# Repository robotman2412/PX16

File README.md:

# Pixie 16
A 16-bit simple-as-possible\* RISC CPU.
Has conditional `MOV` instructions (which is also how branching happens),
And a few math instructions.

Has 4 general registers: `R0`, `R1`, `R2`, `R3`
And 3 special registers: `ST` (stack register), `PF` (flags register), `PC` (program counter)

64K x 16bit memory.

### Note:
RISC is not equal to RISC-V.

PX16 cannot address bytes.

# TODO
Stuf i do be workin on:
- PCB edition
- Emulator
- Finalise MMIO Hardware
- C Compiler

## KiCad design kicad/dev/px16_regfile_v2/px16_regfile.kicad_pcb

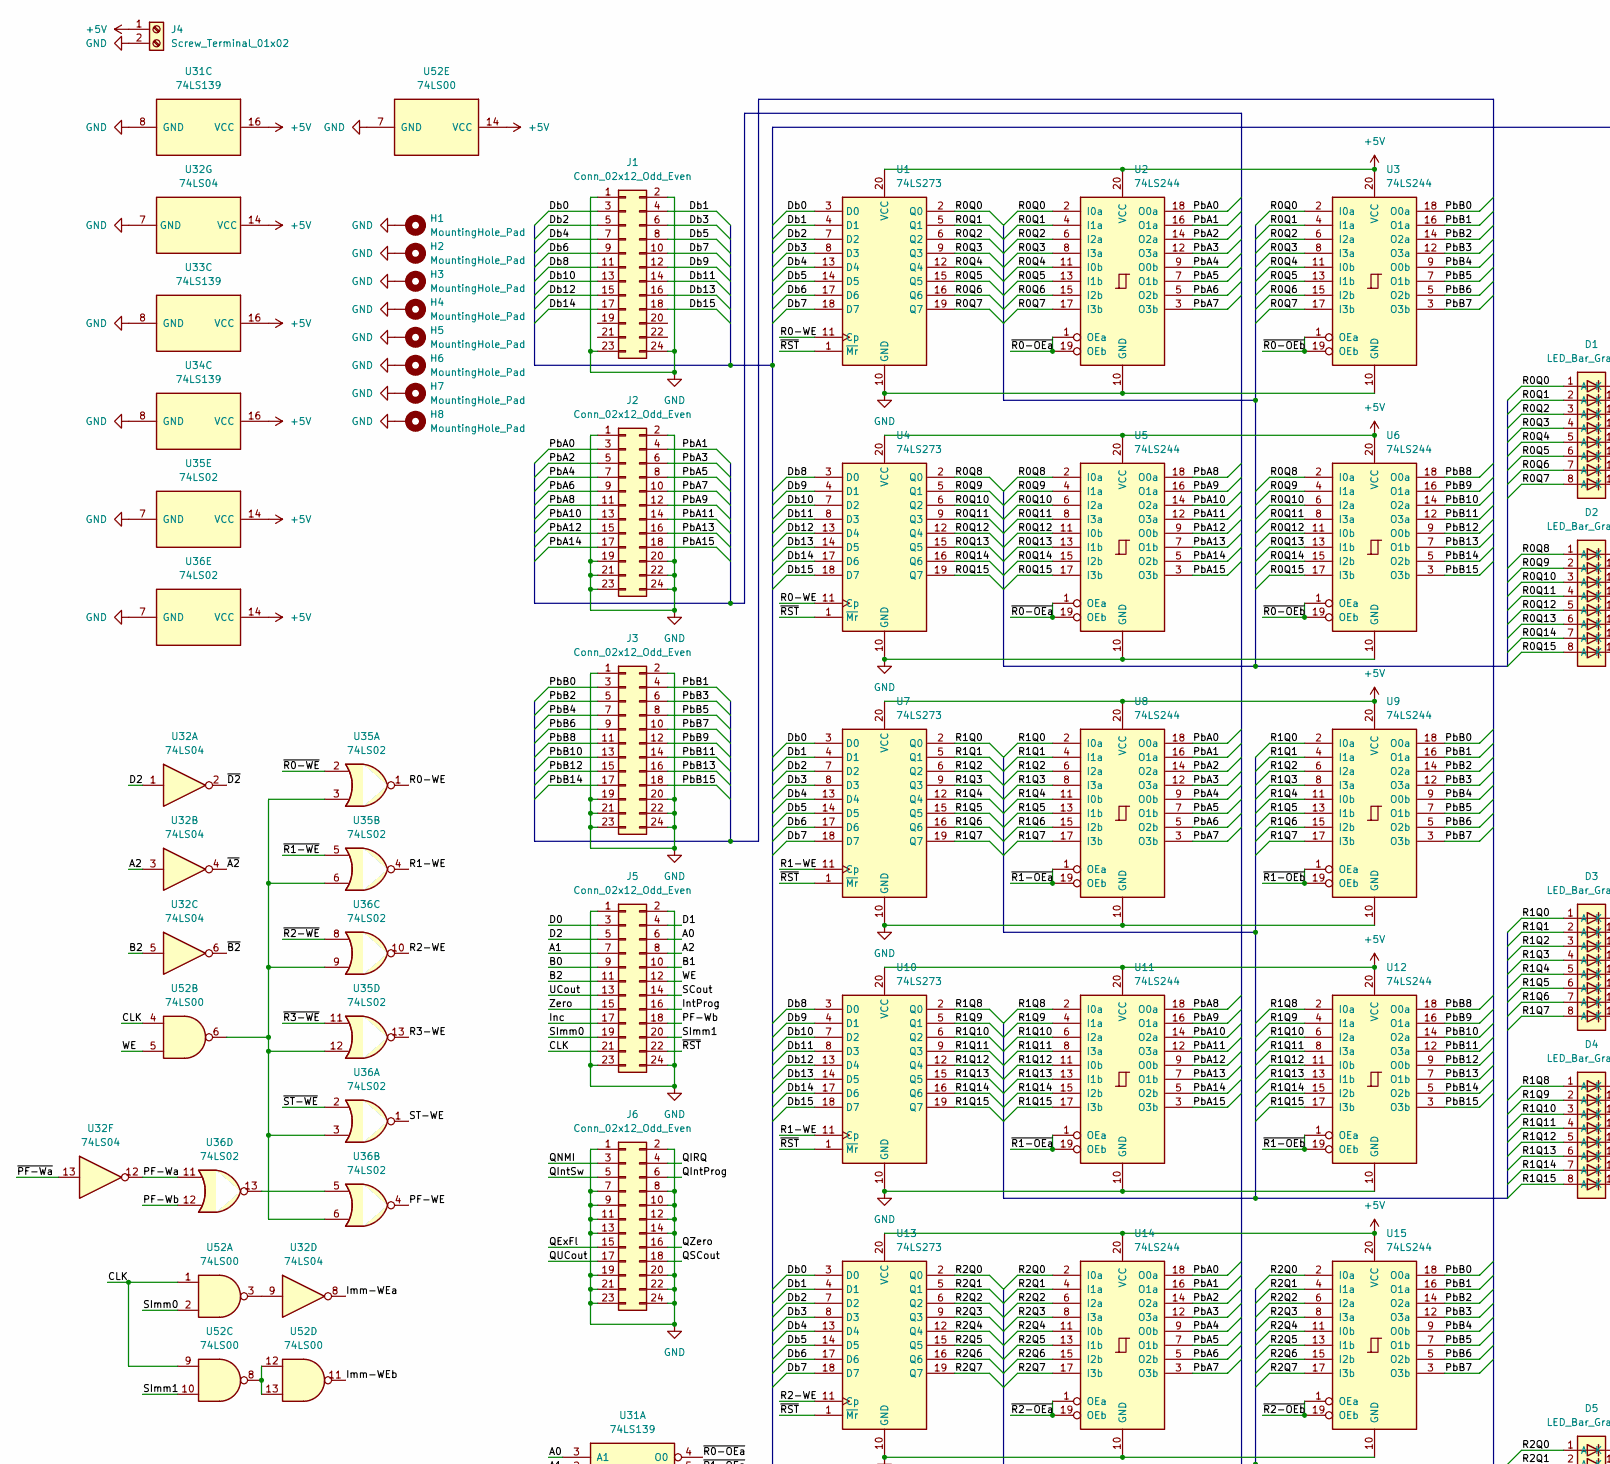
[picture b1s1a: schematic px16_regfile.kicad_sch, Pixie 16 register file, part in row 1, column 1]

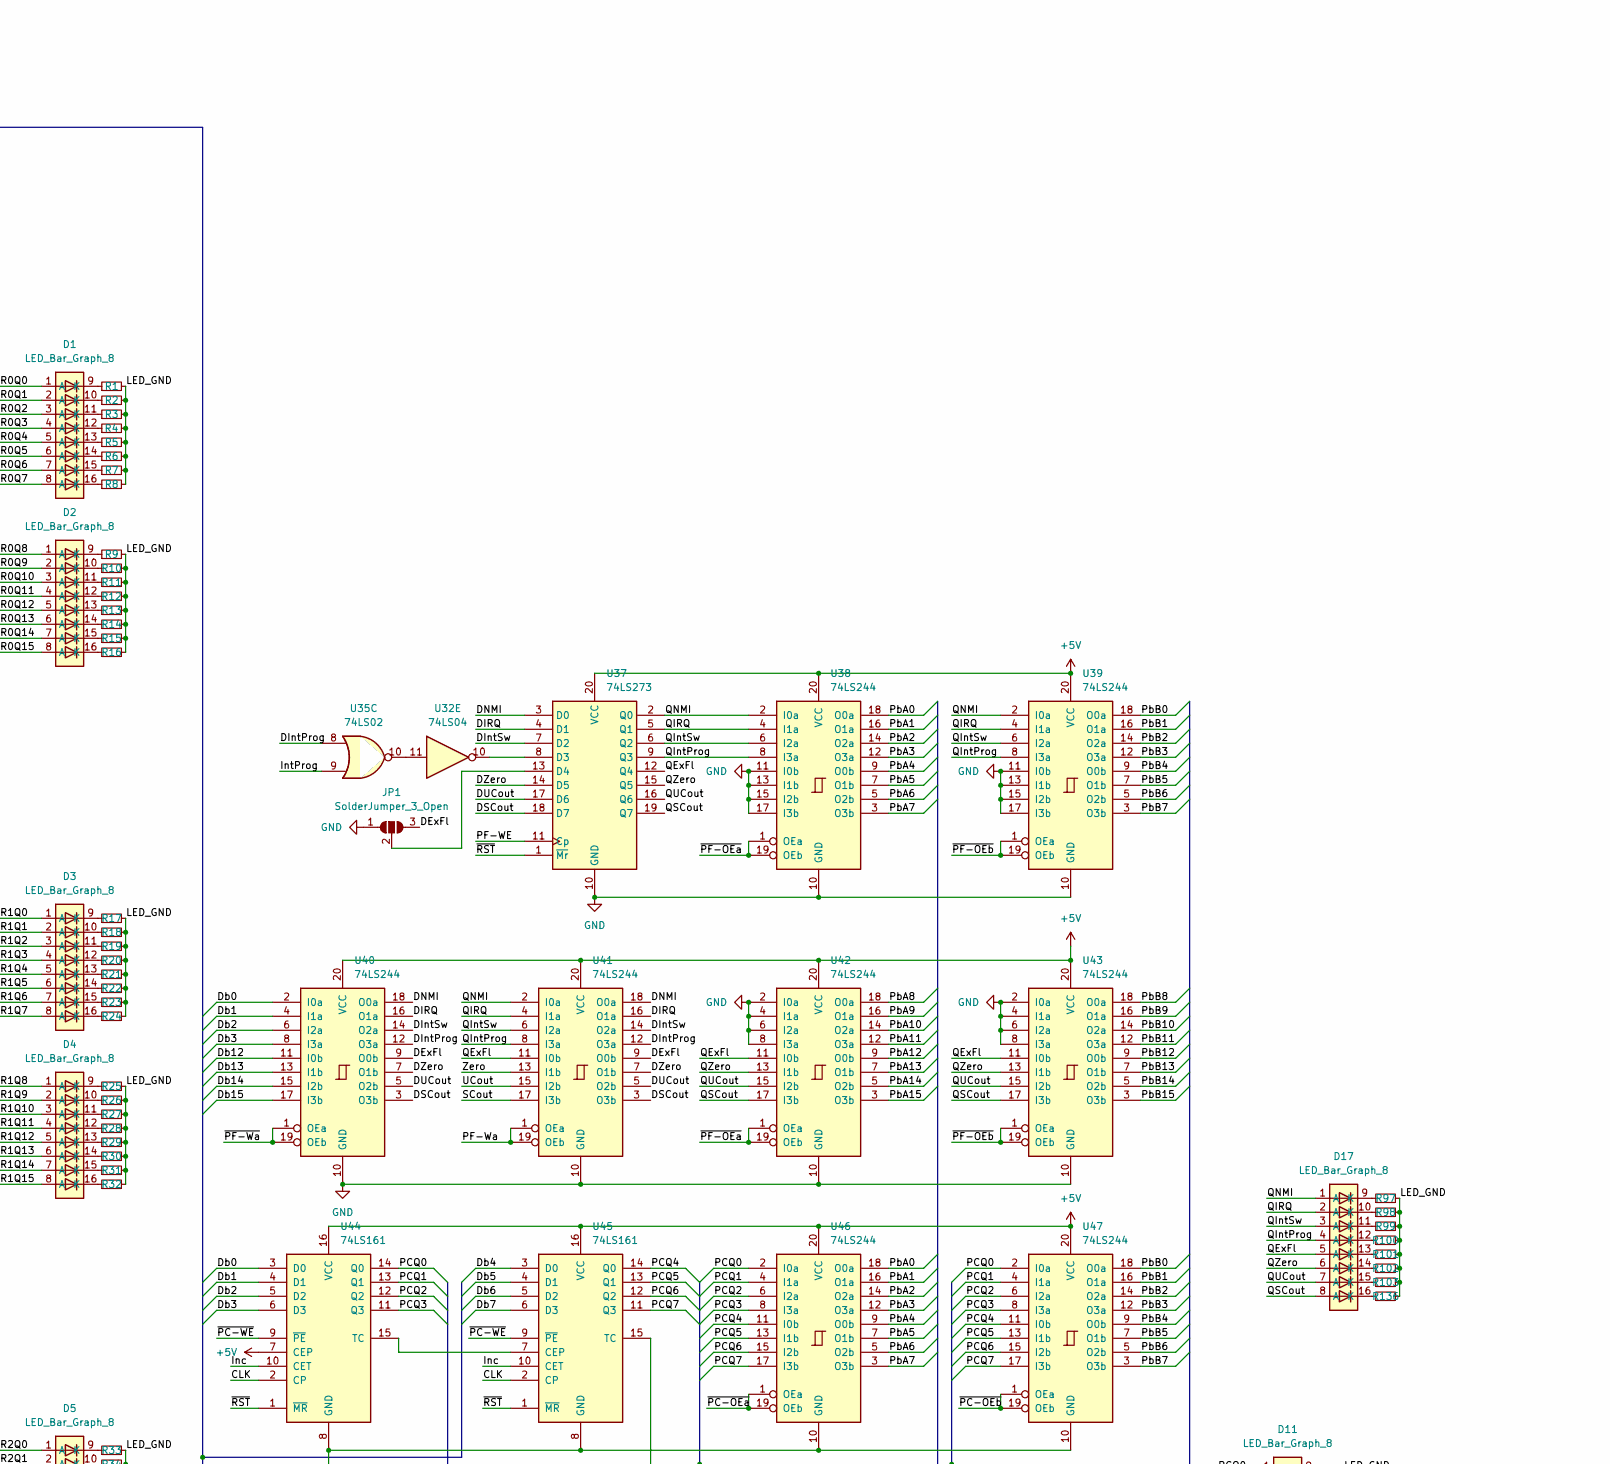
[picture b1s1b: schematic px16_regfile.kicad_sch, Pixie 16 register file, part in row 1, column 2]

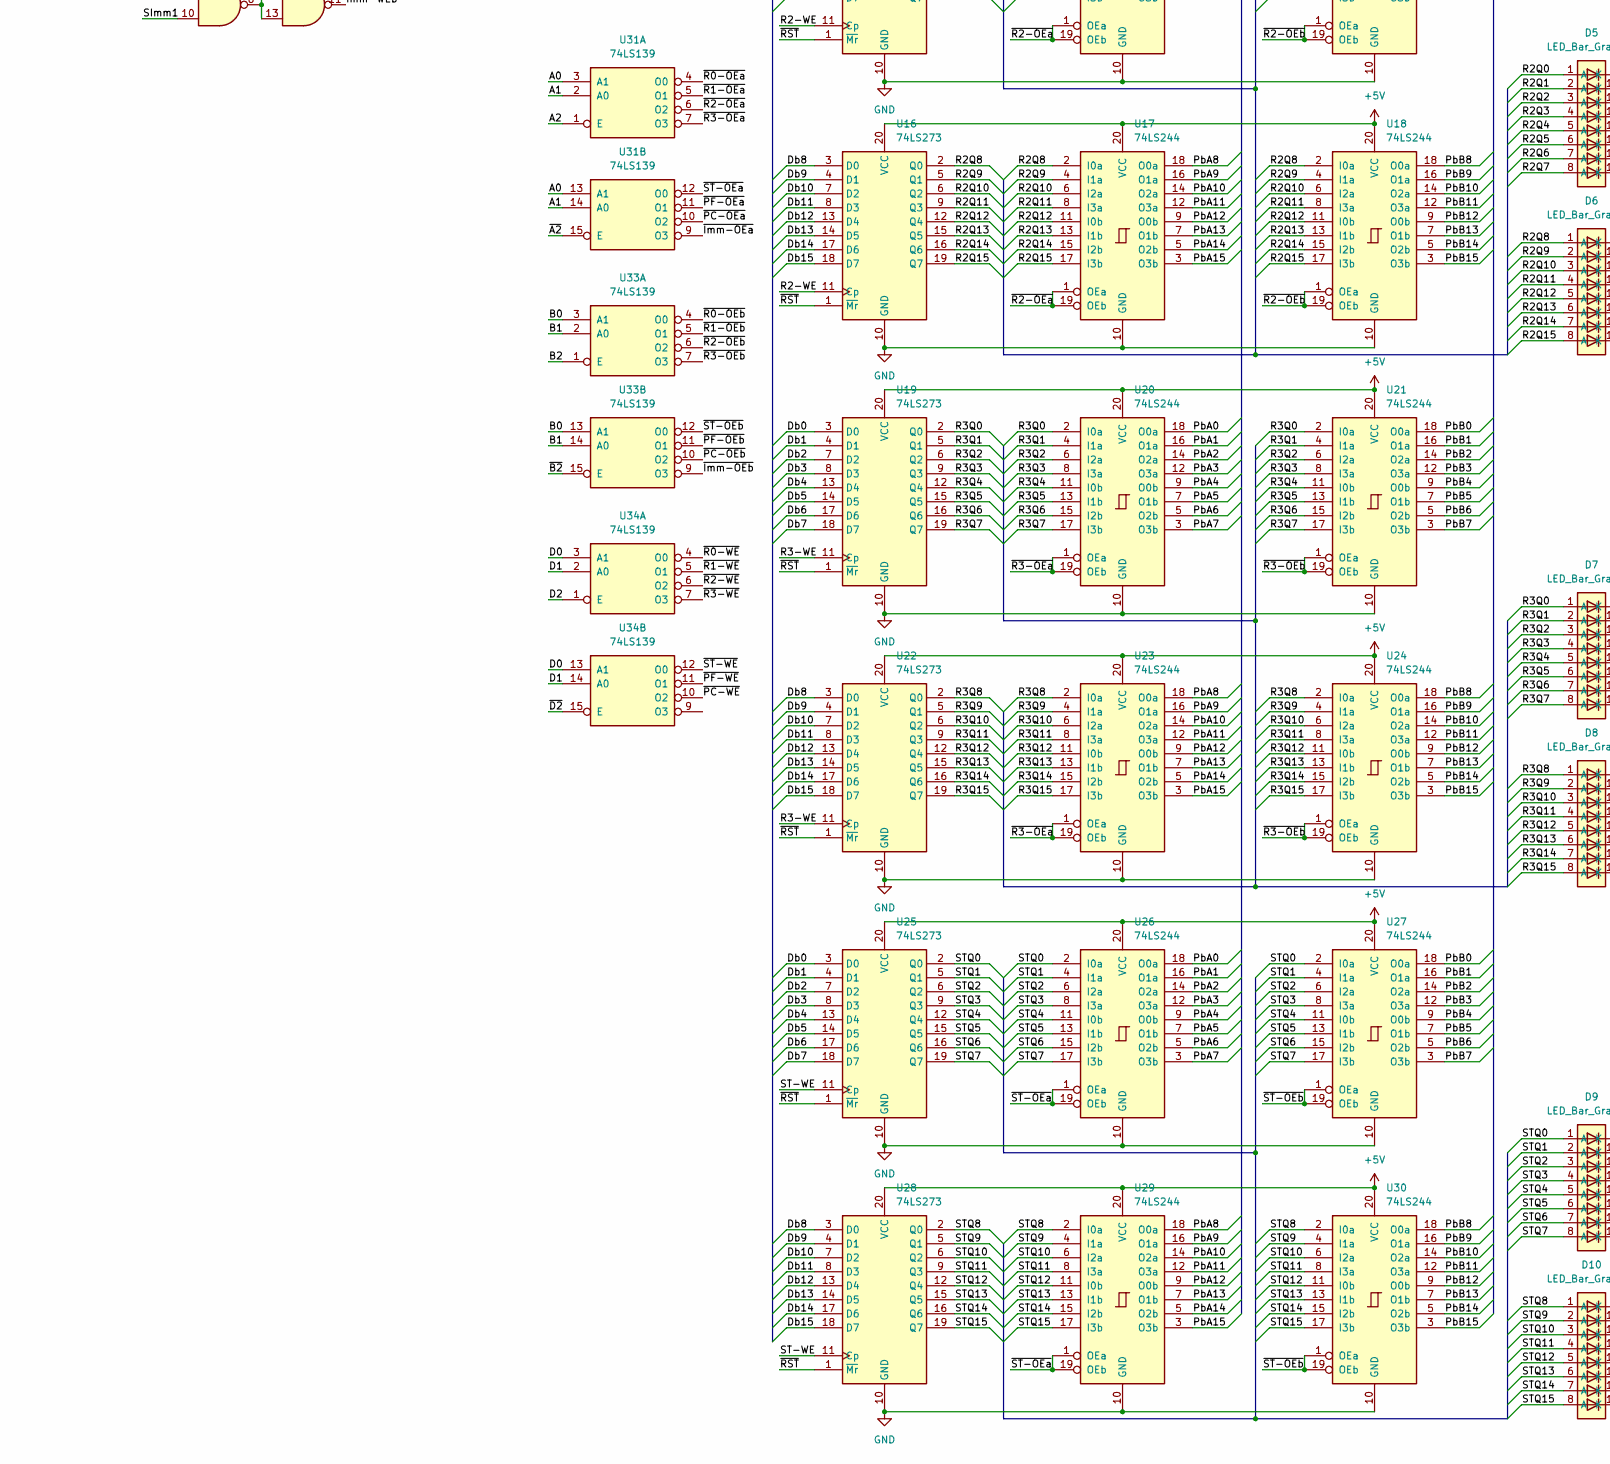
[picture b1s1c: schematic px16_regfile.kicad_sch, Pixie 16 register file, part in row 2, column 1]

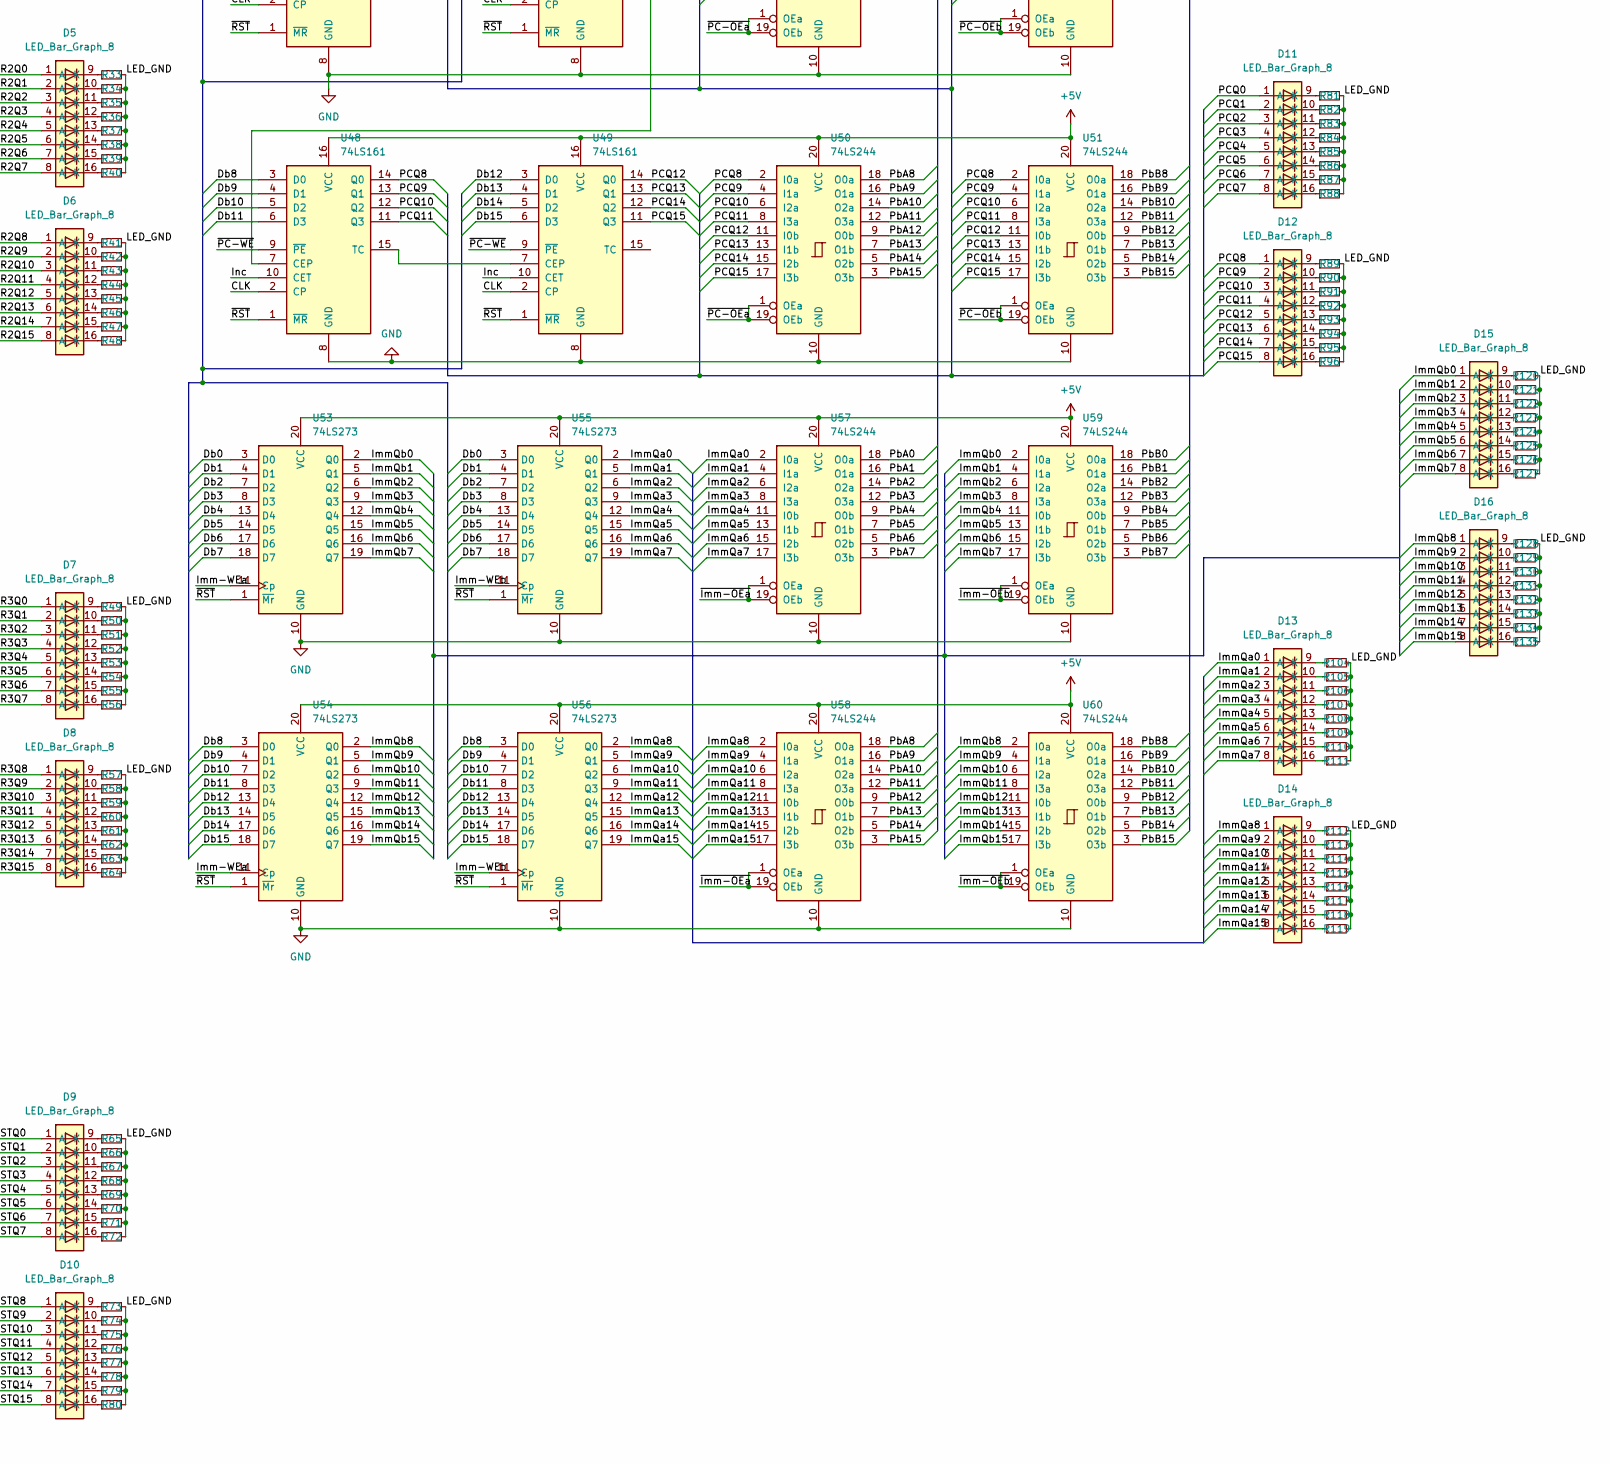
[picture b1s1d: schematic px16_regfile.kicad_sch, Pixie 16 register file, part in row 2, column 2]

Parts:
D1, D2, D3, D4, D5, D6, D7, D8, D9, D10, D11, D12, D13, D14, D15, D16, D17: LED_Bar_Graph_8; DIP-16_W7.62mm_Socket
H1, H2, H3, H4, H5, H6, H7, H8: MountingHole_Pad; MountingHole_3mm_Pad
J1, J2, J3, J5, J6: Conn_02x12_Odd_Even; PinHeader_2x12_P2.54mm_Vertical
J4: Screw_Terminal_01x02; TerminalBlock_bornier-2_P5.08mm
JP1: SolderJumper_3_Open; SolderJumper-3_P1.3mm_Open_Pad1.0x1.5mm_NumberLabels
R1, R2, R3, R4, R5, R6, R7, R8, R9, R10, R11, R12, R13, R14, R15, R16, R17, R18, R19, R20, R21, R22, R23, R24, R25, R26, R27, R28, R29, R30, R31, R32, R33, R34, R35, R36, R37, R38, R39, R40, R41, R42, R43, R44, R45, R46, R47, R48, R49, R50, R51, R52, R53, R54, R55, R56, R57, R58, R59, R60, R61, R62, R63, R64, R65, R66, R67, R68, R69, R70, R71, R72, R73, R74, R75, R76, R77, R78, R79, R80, R81, R82, R83, R84, R85, R86, R87, R88, R89, R90, R91, R92, R93, R94, R95, R96, R97, R98, R99, R100, R101, R102, R103, R104, R105, R106, R107, R108, R109, R110, R111, R112, R113, R114, R115, R116, R117, R118, R119, R120, R121, R122, R123, R124, R125, R126, R127, R128, R129, R130, R131, R132, R133, R134, R135, R136: R; R_Axial_DIN0207_L6.3mm_D2.5mm_P2.54mm_Vertical
U1, U4, U7, U10, U13, U16, U19, U22, U25, U28, U37, U53, U54, U55, U56: 74LS273; SOP-20_7.5x12.8mm_P1.27mm
U2, U3, U5, U6, U8, U9, U11, U12, U14, U15, U17, U18, U20, U21, U23, U24, U26, U27, U29, U30, U38, U39, U40, U41, U42, U43, U46, U47, U50, U51, U57, U58, U59, U60: 74LS244; SOP-20_7.5x12.8mm_P1.27mm
U31, U33, U34: 74LS139; SOIC-16W_7.5x10.3mm_P1.27mm
U32: 74LS04; SOIC-14W_7.5x9mm_P1.27mm
U35, U36: 74LS02; SOIC-14W_7.5x9mm_P1.27mm
U44, U45, U48, U49: 74LS161; SOIC-16W_7.5x10.3mm_P1.27mm
U52: 74LS00; SOIC-14W_7.5x9mm_P1.27mm

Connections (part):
+5V: J4.1, U1.20 (VCC), U2.20 (VCC), U3.20 (VCC), U4.20 (VCC), U5.20 (VCC), U6.20 (VCC), U7.20 (VCC), U8.20 (VCC), U9.20 (VCC), U10.20 (VCC), U11.20 (VCC), U12.20 (VCC), U13.20 (VCC), U14.20 (VCC), U15.20 (VCC), U16.20 (VCC), U17.20 (VCC), U18.20 (VCC), U19.20 (VCC), U20.20 (VCC), U21.20 (VCC), U22.20 (VCC), U23.20 (VCC), U24.20 (VCC), U25.20 (VCC), U26.20 (VCC), U27.20 (VCC), U28.20 (VCC), U29.20 (VCC), U30.20 (VCC), U31.16 (VCC), U32.14 (VCC), U33.16 (VCC), U34.16 (VCC), U35.14 (VCC), U36.14 (VCC), U37.20 (VCC), U38.20 (VCC), U39.20 (VCC), U40.20 (VCC), U41.20 (VCC), U42.20 (VCC), U43.20 (VCC), U44.7 (CEP), U44.16 (VCC), U45.16 (VCC), U46.20 (VCC), U47.20 (VCC), U48.16 (VCC), U49.16 (VCC), U50.20 (VCC), U51.20 (VCC), U52.14 (VCC), U53.20 (VCC), U54.20 (VCC), U55.20 (VCC), U56.20 (VCC), U57.20 (VCC), U58.20 (VCC), U59.20 (VCC), U60.20 (VCC)
/A0: J5.6, U31.3 (A1), U31.13 (A1)
/A1: J5.7, U31.2 (A0), U31.14 (A0)
/A2: J5.8, U31.1 (E), U32.3
/B0: J5.9, U33.3 (A1), U33.13 (A1)
/B1: J5.10, U33.2 (A0), U33.14 (A0)
/B2: J5.11, U32.5, U33.1 (E)
/CLK: J5.21, U44.2 (CP), U45.2 (CP), U48.2 (CP), U49.2 (CP), U52.1, U52.4, U52.9
/D0: J5.3, U34.3 (A1), U34.13 (A1)
/D1: J5.4, U34.2 (A0), U34.14 (A0)
/D2: J5.5, U32.1, U34.1 (E)
/DExFl: JP1.3 (B), U40.9 (O0b), U41.9 (O0b)
/DIRQ: U37.4 (D1), U40.16 (O1a), U41.16 (O1a)
/DIntProg: U35.8, U40.12 (O3a), U41.12 (O3a)
/DIntSw: U37.7 (D2), U40.14 (O2a), U41.14 (O2a)
/DNMI: U37.3 (D0), U40.18 (O0a), U41.18 (O0a)
/DSCout: U37.18 (D7), U40.3 (O3b), U41.3 (O3b)
/DUCout: U37.17 (D6), U40.5 (O2b), U41.5 (O2b)
/DZero: U37.14 (D5), U40.7 (O1b), U41.7 (O1b)
/Db0: J1.3, U1.3 (D0), U7.3 (D0), U13.3 (D0), U19.3 (D0), U25.3 (D0), U40.2 (I0a), U44.3 (D0), U53.3 (D0), U55.3 (D0)
/Db1: J1.4, U1.4 (D1), U7.4 (D1), U13.4 (D1), U19.4 (D1), U25.4 (D1), U40.4 (I1a), U44.4 (D1), U53.4 (D1), U55.4 (D1)
/Db2: J1.5, U1.7 (D2), U7.7 (D2), U13.7 (D2), U19.7 (D2), U25.7 (D2), U40.6 (I2a), U44.5 (D2), U53.7 (D2), U55.7 (D2)
/Db3: J1.6, U1.8 (D3), U7.8 (D3), U13.8 (D3), U19.8 (D3), U25.8 (D3), U40.8 (I3a), U44.6 (D3), U53.8 (D3), U55.8 (D3)
/Db4: J1.7, U1.13 (D4), U7.13 (D4), U13.13 (D4), U19.13 (D4), U25.13 (D4), U45.3 (D0), U53.13 (D4), U55.13 (D4)
/Db5: J1.8, U1.14 (D5), U7.14 (D5), U13.14 (D5), U19.14 (D5), U25.14 (D5), U45.4 (D1), U53.14 (D5), U55.14 (D5)
/Db6: J1.9, U1.17 (D6), U7.17 (D6), U13.17 (D6), U19.17 (D6), U25.17 (D6), U45.5 (D2), U53.17 (D6), U55.17 (D6)
/Db7: J1.10, U1.18 (D7), U7.18 (D7), U13.18 (D7), U19.18 (D7), U25.18 (D7), U45.6 (D3), U53.18 (D7), U55.18 (D7)
/Db8: J1.11, U4.3 (D0), U10.3 (D0), U16.3 (D0), U22.3 (D0), U28.3 (D0), U48.3 (D0), U54.3 (D0), U56.3 (D0)
/Db9: J1.12, U4.4 (D1), U10.4 (D1), U16.4 (D1), U22.4 (D1), U28.4 (D1), U48.4 (D1), U54.4 (D1), U56.4 (D1)
/Db10: J1.13, U4.7 (D2), U10.7 (D2), U16.7 (D2), U22.7 (D2), U28.7 (D2), U48.5 (D2), U54.7 (D2), U56.7 (D2)
/Db11: J1.14, U4.8 (D3), U10.8 (D3), U16.8 (D3), U22.8 (D3), U28.8 (D3), U48.6 (D3), U54.8 (D3), U56.8 (D3)
/Db12: J1.15, U4.13 (D4), U10.13 (D4), U16.13 (D4), U22.13 (D4), U28.13 (D4), U40.11 (I0b), U49.3 (D0), U54.13 (D4), U56.13 (D4)
/Db13: J1.16, U4.14 (D5), U10.14 (D5), U16.14 (D5), U22.14 (D5), U28.14 (D5), U40.13 (I1b), U49.4 (D1), U54.14 (D5), U56.14 (D5)
/Db14: J1.17, U4.17 (D6), U10.17 (D6), U16.17 (D6), U22.17 (D6), U28.17 (D6), U40.15 (I2b), U49.5 (D2), U54.17 (D6), U56.17 (D6)
/Db15: J1.18, U4.18 (D7), U10.18 (D7), U16.18 (D7), U22.18 (D7), U28.18 (D7), U40.17 (I3b), U49.6 (D3), U54.18 (D7), U56.18 (D7)
/Imm-WEa: U32.8, U53.11 (Cp), U54.11 (Cp)
/Imm-WEb: U52.11, U55.11 (Cp), U56.11 (Cp)
/ImmQa0: D13.1 (A), U55.2 (Q0), U57.2 (I0a)
/ImmQa1: D13.2 (A), U55.5 (Q1), U57.4 (I1a)
/ImmQa2: D13.3 (A), U55.6 (Q2), U57.6 (I2a)
/ImmQa3: D13.4 (A), U55.9 (Q3), U57.8 (I3a)
/ImmQa4: D13.5 (A), U55.12 (Q4), U57.11 (I0b)
/ImmQa5: D13.6 (A), U55.15 (Q5), U57.13 (I1b)
/ImmQa6: D13.7 (A), U55.16 (Q6), U57.15 (I2b)
/ImmQa7: D13.8 (A), U55.19 (Q7), U57.17 (I3b)
/ImmQa8: D14.1 (A), U56.2 (Q0), U58.2 (I0a)
/ImmQa9: D14.2 (A), U56.5 (Q1), U58.4 (I1a)
/ImmQa10: D14.3 (A), U56.6 (Q2), U58.6 (I2a)
/ImmQa11: D14.4 (A), U56.9 (Q3), U58.8 (I3a)
/ImmQa12: D14.5 (A), U56.12 (Q4), U58.11 (I0b)
/ImmQa13: D14.6 (A), U56.15 (Q5), U58.13 (I1b)
/ImmQa14: D14.7 (A), U56.16 (Q6), U58.15 (I2b)
/ImmQa15: D14.8 (A), U56.19 (Q7), U58.17 (I3b)
/ImmQb0: D15.1 (A), U53.2 (Q0), U59.2 (I0a)
/ImmQb1: D15.2 (A), U53.5 (Q1), U59.4 (I1a)
/ImmQb2: D15.3 (A), U53.6 (Q2), U59.6 (I2a)
/ImmQb3: D15.4 (A), U53.9 (Q3), U59.8 (I3a)
/ImmQb4: D15.5 (A), U53.12 (Q4), U59.11 (I0b)
/ImmQb5: D15.6 (A), U53.15 (Q5), U59.13 (I1b)
/ImmQb6: D15.7 (A), U53.16 (Q6), U59.15 (I2b)
/ImmQb7: D15.8 (A), U53.19 (Q7), U59.17 (I3b)
/ImmQb8: D16.1 (A), U54.2 (Q0), U60.2 (I0a)
/ImmQb9: D16.2 (A), U54.5 (Q1), U60.4 (I1a)
/ImmQb10: D16.3 (A), U54.6 (Q2), U60.6 (I2a)
/ImmQb11: D16.4 (A), U54.9 (Q3), U60.8 (I3a)
/ImmQb12: D16.5 (A), U54.12 (Q4), U60.11 (I0b)
/ImmQb13: D16.6 (A), U54.15 (Q5), U60.13 (I1b)
/ImmQb14: D16.7 (A), U54.16 (Q6), U60.15 (I2b)
/ImmQb15: D16.8 (A), U54.19 (Q7), U60.17 (I3b)
/Inc: J5.17, U44.10 (CET), U45.10 (CET), U48.10 (CET), U49.10 (CET)
/IntProg: J5.16, U35.9
/LED_GND: R1.2, R2.2, R3.2, R4.2, R5.2, R6.2, R7.2, R8.2, R9.2, R10.2, R11.2, R12.2, R13.2, R14.2, R15.2, R16.2, R17.2, R18.2, R19.2, R20.2, R21.2, R22.2, R23.2, R24.2, R25.2, R26.2, R27.2, R28.2, R29.2, R30.2, R31.2, R32.2, R33.2, R34.2, R35.2, R36.2, R37.2, R38.2, R39.2, R40.2, R41.2, R42.2, R43.2, R44.2, R45.2, R46.2, R47.2, R48.2, R49.2, R50.2, R51.2, R52.2, R53.2, R54.2, R55.2, R56.2, R57.2, R58.2, R59.2, R60.2, R61.2, R62.2, R63.2, R64.2, R65.2, R66.2, R67.2, R68.2, R69.2, R70.2, R71.2, R72.2, R73.2, R74.2, R75.2, R76.2, R77.2, R78.2, R79.2, R80.2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
/PCQ0: D11.1 (A), U44.14 (Q0), U46.2 (I0a), U47.2 (I0a)
/PCQ1: D11.2 (A), U44.13 (Q1), U46.4 (I1a), U47.4 (I1a)
/PCQ2: D11.3 (A), U44.12 (Q2), U46.6 (I2a), U47.6 (I2a)
/PCQ3: D11.4 (A), U44.11 (Q3), U46.8 (I3a), U47.8 (I3a)
/PCQ4: D11.5 (A), U45.14 (Q0), U46.11 (I0b), U47.11 (I0b)
/PCQ5: D11.6 (A), U45.13 (Q1), U46.13 (I1b), U47.13 (I1b)
/PCQ6: D11.7 (A), U45.12 (Q2), U46.15 (I2b), U47.15 (I2b)
/PCQ7: D11.8 (A), U45.11 (Q3), U46.17 (I3b), U47.17 (I3b)
/PCQ8: D12.1 (A), U48.14 (Q0), U50.2 (I0a), U51.2 (I0a)
/PCQ9: D12.2 (A), U48.13 (Q1), U50.4 (I1a), U51.4 (I1a)
/PCQ10: D12.3 (A), U48.12 (Q2), U50.6 (I2a), U51.6 (I2a)
/PCQ11: D12.4 (A), U48.11 (Q3), U50.8 (I3a), U51.8 (I3a)
/PCQ12: D12.5 (A), U49.14 (Q0), U50.11 (I0b), U51.11 (I0b)
/PCQ13: D12.6 (A), U49.13 (Q1), U50.13 (I1b), U51.13 (I1b)
/PCQ14: D12.7 (A), U49.12 (Q2), U50.15 (I2b), U51.15 (I2b)
/PCQ15: D12.8 (A), U49.11 (Q3), U50.17 (I3b), U51.17 (I3b)
/PF-WE: U36.4, U37.11 (Cp)
/PF-Wa: U32.12, U36.11, U41.1 (OEa), U41.19 (OEb)
/PF-Wb: J5.18, U36.12
/PbA0: J2.3, U2.18 (O0a), U8.18 (O0a), U14.18 (O0a), U20.18 (O0a), U26.18 (O0a), U38.18 (O0a), U46.18 (O0a), U57.18 (O0a)
/PbA1: J2.4, U2.16 (O1a), U8.16 (O1a), U14.16 (O1a), U20.16 (O1a), U26.16 (O1a), U38.16 (O1a), U46.16 (O1a), U57.16 (O1a)
/PbA2: J2.5, U2.14 (O2a), U8.14 (O2a), U14.14 (O2a), U20.14 (O2a), U26.14 (O2a), U38.14 (O2a), U46.14 (O2a), U57.14 (O2a)
/PbA3: J2.6, U2.12 (O3a), U8.12 (O3a), U14.12 (O3a), U20.12 (O3a), U26.12 (O3a), U38.12 (O3a), U46.12 (O3a), U57.12 (O3a)
/PbA4: J2.7, U2.9 (O0b), U8.9 (O0b), U14.9 (O0b), U20.9 (O0b), U26.9 (O0b), U38.9 (O0b), U46.9 (O0b), U57.9 (O0b)
/PbA5: J2.8, U2.7 (O1b), U8.7 (O1b), U14.7 (O1b), U20.7 (O1b), U26.7 (O1b), U38.7 (O1b), U46.7 (O1b), U57.7 (O1b)
/PbA6: J2.9, U2.5 (O2b), U8.5 (O2b), U14.5 (O2b), U20.5 (O2b), U26.5 (O2b), U38.5 (O2b), U46.5 (O2b), U57.5 (O2b)
/PbA7: J2.10, U2.3 (O3b), U8.3 (O3b), U14.3 (O3b), U20.3 (O3b), U26.3 (O3b), U38.3 (O3b), U46.3 (O3b), U57.3 (O3b)
/PbA8: J2.11, U5.18 (O0a), U11.18 (O0a), U17.18 (O0a), U23.18 (O0a), U29.18 (O0a), U42.18 (O0a), U50.18 (O0a), U58.18 (O0a)
/PbA9: J2.12, U5.16 (O1a), U11.16 (O1a), U17.16 (O1a), U23.16 (O1a), U29.16 (O1a), U42.16 (O1a), U50.16 (O1a), U58.16 (O1a)
/PbA10: J2.13, U5.14 (O2a), U11.14 (O2a), U17.14 (O2a), U23.14 (O2a), U29.14 (O2a), U42.14 (O2a), U50.14 (O2a), U58.14 (O2a)
/PbA11: J2.14, U5.12 (O3a), U11.12 (O3a), U17.12 (O3a), U23.12 (O3a), U29.12 (O3a), U42.12 (O3a), U50.12 (O3a), U58.12 (O3a)
/PbA12: J2.15, U5.9 (O0b), U11.9 (O0b), U17.9 (O0b), U23.9 (O0b), U29.9 (O0b), U42.9 (O0b), U50.9 (O0b), U58.9 (O0b)
/PbA13: J2.16, U5.7 (O1b), U11.7 (O1b), U17.7 (O1b), U23.7 (O1b), U29.7 (O1b), U42.7 (O1b), U50.7 (O1b), U58.7 (O1b)
/PbA14: J2.17, U5.5 (O2b), U11.5 (O2b), U17.5 (O2b), U23.5 (O2b), U29.5 (O2b), U42.5 (O2b), U50.5 (O2b), U58.5 (O2b)
/PbA15: J2.18, U5.3 (O3b), U11.3 (O3b), U17.3 (O3b), U23.3 (O3b), U29.3 (O3b), U42.3 (O3b), U50.3 (O3b), U58.3 (O3b)
/PbB0: J3.3, U3.18 (O0a), U9.18 (O0a), U15.18 (O0a), U21.18 (O0a), U27.18 (O0a), U39.18 (O0a), U47.18 (O0a), U59.18 (O0a)
/PbB1: J3.4, U3.16 (O1a), U9.16 (O1a), U15.16 (O1a), U21.16 (O1a), U27.16 (O1a), U39.16 (O1a), U47.16 (O1a), U59.16 (O1a)
/PbB2: J3.5, U3.14 (O2a), U9.14 (O2a), U15.14 (O2a), U21.14 (O2a), U27.14 (O2a), U39.14 (O2a), U47.14 (O2a), U59.14 (O2a)
/PbB3: J3.6, U3.12 (O3a), U9.12 (O3a), U15.12 (O3a), U21.12 (O3a), U27.12 (O3a), U39.12 (O3a), U47.12 (O3a), U59.12 (O3a)
/PbB4: J3.7, U3.9 (O0b), U9.9 (O0b), U15.9 (O0b), U21.9 (O0b), U27.9 (O0b), U39.9 (O0b), U47.9 (O0b), U59.9 (O0b)
/PbB5: J3.8, U3.7 (O1b), U9.7 (O1b), U15.7 (O1b), U21.7 (O1b), U27.7 (O1b), U39.7 (O1b), U47.7 (O1b), U59.7 (O1b)
/PbB6: J3.9, U3.5 (O2b), U9.5 (O2b), U15.5 (O2b), U21.5 (O2b), U27.5 (O2b), U39.5 (O2b), U47.5 (O2b), U59.5 (O2b)
/PbB7: J3.10, U3.3 (O3b), U9.3 (O3b), U15.3 (O3b), U21.3 (O3b), U27.3 (O3b), U39.3 (O3b), U47.3 (O3b), U59.3 (O3b)
/PbB8: J3.11, U6.18 (O0a), U12.18 (O0a), U18.18 (O0a), U24.18 (O0a), U30.18 (O0a), U43.18 (O0a), U51.18 (O0a), U60.18 (O0a)
/PbB9: J3.12, U6.16 (O1a), U12.16 (O1a), U18.16 (O1a), U24.16 (O1a), U30.16 (O1a), U43.16 (O1a), U51.16 (O1a), U60.16 (O1a)
/PbB10: J3.13, U6.14 (O2a), U12.14 (O2a), U18.14 (O2a), U24.14 (O2a), U30.14 (O2a), U43.14 (O2a), U51.14 (O2a), U60.14 (O2a)
/PbB11: J3.14, U6.12 (O3a), U12.12 (O3a), U18.12 (O3a), U24.12 (O3a), U30.12 (O3a), U43.12 (O3a), U51.12 (O3a), U60.12 (O3a)
/PbB12: J3.15, U6.9 (O0b), U12.9 (O0b), U18.9 (O0b), U24.9 (O0b), U30.9 (O0b), U43.9 (O0b), U51.9 (O0b), U60.9 (O0b)
/PbB13: J3.16, U6.7 (O1b), U12.7 (O1b), U18.7 (O1b), U24.7 (O1b), U30.7 (O1b), U43.7 (O1b), U51.7 (O1b), U60.7 (O1b)
/PbB14: J3.17, U6.5 (O2b), U12.5 (O2b), U18.5 (O2b), U24.5 (O2b), U30.5 (O2b), U43.5 (O2b), U51.5 (O2b), U60.5 (O2b)
/PbB15: J3.18, U6.3 (O3b), U12.3 (O3b), U18.3 (O3b), U24.3 (O3b), U30.3 (O3b), U43.3 (O3b), U51.3 (O3b), U60.3 (O3b)
/QExFl: D17.5 (A), J6.15, U37.12 (Q4), U41.11 (I0b), U42.11 (I0b), U43.11 (I0b)
/QIRQ: D17.2 (A), J6.4, U37.5 (Q1), U38.4 (I1a), U39.4 (I1a), U41.4 (I1a)
/QIntProg: D17.4 (A), J6.6, U37.9 (Q3), U38.8 (I3a), U39.8 (I3a), U41.8 (I3a)
/QIntSw: D17.3 (A), J6.5, U37.6 (Q2), U38.6 (I2a), U39.6 (I2a), U41.6 (I2a)
/QNMI: D17.1 (A), J6.3, U37.2 (Q0), U38.2 (I0a), U39.2 (I0a), U41.2 (I0a)
/QSCout: D17.8 (A), J6.18, U37.19 (Q7), U42.17 (I3b), U43.17 (I3b)
/QUCout: D17.7 (A), J6.17, U37.16 (Q6), U42.15 (I2b), U43.15 (I2b)
/QZero: D17.6 (A), J6.16, U37.15 (Q5), U42.13 (I1b), U43.13 (I1b)
/R0-WE: U1.11 (Cp), U4.11 (Cp), U35.1
/R0Q0: D1.1 (A), U1.2 (Q0), U2.2 (I0a), U3.2 (I0a)
/R0Q1: D1.2 (A), U1.5 (Q1), U2.4 (I1a), U3.4 (I1a)
/R0Q2: D1.3 (A), U1.6 (Q2), U2.6 (I2a), U3.6 (I2a)
/R0Q3: D1.4 (A), U1.9 (Q3), U2.8 (I3a), U3.8 (I3a)
/R0Q4: D1.5 (A), U1.12 (Q4), U2.11 (I0b), U3.11 (I0b)
/R0Q5: D1.6 (A), U1.15 (Q5), U2.13 (I1b), U3.13 (I1b)
/R0Q6: D1.7 (A), U1.16 (Q6), U2.15 (I2b), U3.15 (I2b)
/R0Q7: D1.8 (A), U1.19 (Q7), U2.17 (I3b), U3.17 (I3b)
/R0Q8: D2.1 (A), U4.2 (Q0), U5.2 (I0a), U6.2 (I0a)
/R0Q9: D2.2 (A), U4.5 (Q1), U5.4 (I1a), U6.4 (I1a)
/R0Q10: D2.3 (A), U4.6 (Q2), U5.6 (I2a), U6.6 (I2a)
/R0Q11: D2.4 (A), U4.9 (Q3), U5.8 (I3a), U6.8 (I3a)
/R0Q12: D2.5 (A), U4.12 (Q4), U5.11 (I0b), U6.11 (I0b)
/R0Q13: D2.6 (A), U4.15 (Q5), U5.13 (I1b), U6.13 (I1b)
/R0Q14: D2.7 (A), U4.16 (Q6), U5.15 (I2b), U6.15 (I2b)
/R0Q15: D2.8 (A), U4.19 (Q7), U5.17 (I3b), U6.17 (I3b)
/R1-WE: U7.11 (Cp), U10.11 (Cp), U35.4
/R1Q0: D3.1 (A), U7.2 (Q0), U8.2 (I0a), U9.2 (I0a)
/R1Q1: D3.2 (A), U7.5 (Q1), U8.4 (I1a), U9.4 (I1a)
/R1Q2: D3.3 (A), U7.6 (Q2), U8.6 (I2a), U9.6 (I2a)
/R1Q3: D3.4 (A), U7.9 (Q3), U8.8 (I3a), U9.8 (I3a)
/R1Q4: D3.5 (A), U7.12 (Q4), U8.11 (I0b), U9.11 (I0b)
/R1Q5: D3.6 (A), U7.15 (Q5), U8.13 (I1b), U9.13 (I1b)
/R1Q6: D3.7 (A), U7.16 (Q6), U8.15 (I2b), U9.15 (I2b)
/R1Q7: D3.8 (A), U7.19 (Q7), U8.17 (I3b), U9.17 (I3b)
/R1Q8: D4.1 (A), U10.2 (Q0), U11.2 (I0a), U12.2 (I0a)
/R1Q9: D4.2 (A), U10.5 (Q1), U11.4 (I1a), U12.4 (I1a)
/R1Q10: D4.3 (A), U10.6 (Q2), U11.6 (I2a), U12.6 (I2a)
/R1Q11: D4.4 (A), U10.9 (Q3), U11.8 (I3a), U12.8 (I3a)
/R1Q12: D4.5 (A), U10.12 (Q4), U11.11 (I0b), U12.11 (I0b)
/R1Q13: D4.6 (A), U10.15 (Q5), U11.13 (I1b), U12.13 (I1b)
/R1Q14: D4.7 (A), U10.16 (Q6), U11.15 (I2b), U12.15 (I2b)
/R1Q15: D4.8 (A), U10.19 (Q7), U11.17 (I3b), U12.17 (I3b)
/R2-WE: U13.11 (Cp), U16.11 (Cp), U36.10
/R2Q0: D5.1 (A), U13.2 (Q0), U14.2 (I0a), U15.2 (I0a)
/R2Q1: D5.2 (A), U13.5 (Q1), U14.4 (I1a), U15.4 (I1a)
/R2Q2: D5.3 (A), U13.6 (Q2), U14.6 (I2a), U15.6 (I2a)
/R2Q3: D5.4 (A), U13.9 (Q3), U14.8 (I3a), U15.8 (I3a)
/R2Q4: D5.5 (A), U13.12 (Q4), U14.11 (I0b), U15.11 (I0b)
/R2Q5: D5.6 (A), U13.15 (Q5), U14.13 (I1b), U15.13 (I1b)
/R2Q6: D5.7 (A), U13.16 (Q6), U14.15 (I2b), U15.15 (I2b)
/R2Q7: D5.8 (A), U13.19 (Q7), U14.17 (I3b), U15.17 (I3b)
/R2Q8: D6.1 (A), U16.2 (Q0), U17.2 (I0a), U18.2 (I0a)
/R2Q9: D6.2 (A), U16.5 (Q1), U17.4 (I1a), U18.4 (I1a)
/R2Q10: D6.3 (A), U16.6 (Q2), U17.6 (I2a), U18.6 (I2a)
/R2Q11: D6.4 (A), U16.9 (Q3), U17.8 (I3a), U18.8 (I3a)
/R2Q12: D6.5 (A), U16.12 (Q4), U17.11 (I0b), U18.11 (I0b)
/R2Q13: D6.6 (A), U16.15 (Q5), U17.13 (I1b), U18.13 (I1b)
/R2Q14: D6.7 (A), U16.16 (Q6), U17.15 (I2b), U18.15 (I2b)
/R2Q15: D6.8 (A), U16.19 (Q7), U17.17 (I3b), U18.17 (I3b)
/R3-WE: U19.11 (Cp), U22.11 (Cp), U35.13
/R3Q0: D7.1 (A), U19.2 (Q0), U20.2 (I0a), U21.2 (I0a)
/R3Q1: D7.2 (A), U19.5 (Q1), U20.4 (I1a), U21.4 (I1a)
/R3Q2: D7.3 (A), U19.6 (Q2), U20.6 (I2a), U21.6 (I2a)
/R3Q3: D7.4 (A), U19.9 (Q3), U20.8 (I3a), U21.8 (I3a)
/R3Q4: D7.5 (A), U19.12 (Q4), U20.11 (I0b), U21.11 (I0b)
/R3Q5: D7.6 (A), U19.15 (Q5), U20.13 (I1b), U21.13 (I1b)
/R3Q6: D7.7 (A), U19.16 (Q6), U20.15 (I2b), U21.15 (I2b)
/R3Q7: D7.8 (A), U19.19 (Q7), U20.17 (I3b), U21.17 (I3b)
/R3Q8: D8.1 (A), U22.2 (Q0), U23.2 (I0a), U24.2 (I0a)
/R3Q9: D8.2 (A), U22.5 (Q1), U23.4 (I1a), U24.4 (I1a)
/R3Q10: D8.3 (A), U22.6 (Q2), U23.6 (I2a), U24.6 (I2a)
/R3Q11: D8.4 (A), U22.9 (Q3), U23.8 (I3a), U24.8 (I3a)
/R3Q12: D8.5 (A), U22.12 (Q4), U23.11 (I0b), U24.11 (I0b)
/R3Q13: D8.6 (A), U22.15 (Q5), U23.13 (I1b), U24.13 (I1b)
/R3Q14: D8.7 (A), U22.16 (Q6), U23.15 (I2b), U24.15 (I2b)
/R3Q15: D8.8 (A), U22.19 (Q7), U23.17 (I3b), U24.17 (I3b)
/SCout: J5.14, U41.17 (I3b)
/SImm0: J5.19, U52.2
/SImm1: J5.20, U52.10
/ST-WE: U25.11 (Cp), U28.11 (Cp), U36.1
/STQ0: D9.1 (A), U25.2 (Q0), U26.2 (I0a), U27.2 (I0a)
/STQ1: D9.2 (A), U25.5 (Q1), U26.4 (I1a), U27.4 (I1a)
/STQ2: D9.3 (A), U25.6 (Q2), U26.6 (I2a), U27.6 (I2a)
/STQ3: D9.4 (A), U25.9 (Q3), U26.8 (I3a), U27.8 (I3a)
/STQ4: D9.5 (A), U25.12 (Q4), U26.11 (I0b), U27.11 (I0b)
/STQ5: D9.6 (A), U25.15 (Q5), U26.13 (I1b), U27.13 (I1b)
/STQ6: D9.7 (A), U25.16 (Q6), U26.15 (I2b), U27.15 (I2b)
/STQ7: D9.8 (A), U25.19 (Q7), U26.17 (I3b), U27.17 (I3b)
/STQ8: D10.1 (A), U28.2 (Q0), U29.2 (I0a), U30.2 (I0a)
/STQ9: D10.2 (A), U28.5 (Q1), U29.4 (I1a), U30.4 (I1a)
/STQ10: D10.3 (A), U28.6 (Q2), U29.6 (I2a), U30.6 (I2a)
/STQ11: D10.4 (A), U28.9 (Q3), U29.8 (I3a), U30.8 (I3a)
/STQ12: D10.5 (A), U28.12 (Q4), U29.11 (I0b), U30.11 (I0b)
/STQ13: D10.6 (A), U28.15 (Q5), U29.13 (I1b), U30.13 (I1b)
/STQ14: D10.7 (A), U28.16 (Q6), U29.15 (I2b), U30.15 (I2b)
/STQ15: D10.8 (A), U28.19 (Q7), U29.17 (I3b), U30.17 (I3b)
/UCout: J5.13, U41.15 (I2b)
/WE: J5.12, U52.5
/Zero: J5.15, U41.13 (I1b)
/~A2: U31.15 (E), U32.4
/~B2: U32.6, U33.15 (E)
/~D2: U32.2, U34.15 (E)
/~Imm-OEa: U31.9 (O3), U57.1 (OEa), U57.19 (OEb), U58.1 (OEa), U58.19 (OEb)
/~Imm-OEb: U33.9 (O3), U59.1 (OEa), U59.19 (OEb), U60.1 (OEa), U60.19 (OEb)
/~PC-OEa: U31.10 (O2), U46.1 (OEa), U46.19 (OEb), U50.1 (OEa), U50.19 (OEb)
/~PC-OEb: U33.10 (O2), U47.1 (OEa), U47.19 (OEb), U51.1 (OEa), U51.19 (OEb)
/~PC-WE: U34.10 (O2), U44.9 (~PE), U45.9 (~PE), U48.9 (~PE), U49.9 (~PE)
/~PF-OEa: U31.11 (O1), U38.1 (OEa), U38.19 (OEb), U42.1 (OEa), U42.19 (OEb)
/~PF-OEb: U33.11 (O1), U39.1 (OEa), U39.19 (OEb), U43.1 (OEa), U43.19 (OEb)
/~PF-WE: U34.11 (O1)
/~PF-Wa: U32.13, U40.1 (OEa), U40.19 (OEb)
/~R0-OEa: U2.1 (OEa), U2.19 (OEb), U5.1 (OEa), U5.19 (OEb), U31.4 (O0)
/~R0-OEb: U3.1 (OEa), U3.19 (OEb), U6.1 (OEa), U6.19 (OEb), U33.4 (O0)
/~R0-WE: U34.4 (O0), U35.2
/~R1-OEa: U8.1 (OEa), U8.19 (OEb), U11.1 (OEa), U11.19 (OEb), U31.5 (O1)
/~R1-OEb: U9.1 (OEa), U9.19 (OEb), U12.1 (OEa), U12.19 (OEb), U33.5 (O1)
/~R1-WE: U34.5 (O1), U35.5
/~R2-OEa: U14.1 (OEa), U14.19 (OEb), U17.1 (OEa), U17.19 (OEb), U31.6 (O2)
/~R2-OEb: U15.1 (OEa), U15.19 (OEb), U18.1 (OEa), U18.19 (OEb), U33.6 (O2)
/~R2-WE: U34.6 (O2), U36.8
/~R3-OEa: U20.1 (OEa), U20.19 (OEb), U23.1 (OEa), U23.19 (OEb), U31.7 (O3)
/~R3-OEb: U21.1 (OEa), U21.19 (OEb), U24.1 (OEa), U24.19 (OEb), U33.7 (O3)
/~R3-WE: U34.7 (O3), U35.11
/~RST: J5.22, U1.1 (~Mr), U4.1 (~Mr), U7.1 (~Mr), U10.1 (~Mr), U13.1 (~Mr), U16.1 (~Mr), U19.1 (~Mr), U22.1 (~Mr), U25.1 (~Mr), U28.1 (~Mr), U37.1 (~Mr), U44.1 (~MR), U45.1 (~MR), U48.1 (~MR), U49.1 (~MR), U53.1 (~Mr), U54.1 (~Mr), U55.1 (~Mr), U56.1 (~Mr)
/~ST-OEa: U26.1 (OEa), U26.19 (OEb), U29.1 (OEa), U29.19 (OEb), U31.12 (O0)
/~ST-OEb: U27.1 (OEa), U27.19 (OEb), U30.1 (OEa), U30.19 (OEb), U33.12 (O0)
/~ST-WE: U34.12 (O0), U36.2
GND: H1.1, H2.1, H3.1, H4.1, H5.1, H6.1, H7.1, H8.1, J1.1, J1.2, J1.23, J1.24, J2.1, J2.2, J2.19, J2.20, J2.21, J2.22, J2.23, J2.24, J3.1, J3.2, J3.19, J3.20, J3.21, J3.22, J3.23, J3.24, J4.2, J5.1, J5.2, J5.23, J5.24, J6.1, J6.2, J6.7, J6.8, J6.9, J6.10, J6.11, J6.12, J6.13, J6.14, J6.19, J6.20, J6.21, J6.22, J6.23, J6.24, JP1.1 (A), U1.10 (GND), U2.10 (GND), U3.10 (GND), U4.10 (GND), U5.10 (GND), U6.10 (GND), U7.10 (GND), U8.10 (GND), U9.10 (GND), U10.10 (GND), U11.10 (GND), U12.10 (GND), U13.10 (GND), U14.10 (GND), U15.10 (GND), U16.10 (GND), U17.10 (GND), U18.10 (GND), U19.10 (GND), U20.10 (GND), U21.10 (GND), U22.10 (GND), U23.10 (GND), U24.10 (GND), U25.10 (GND), U26.10 (GND), U27.10 (GND), U28.10 (GND), U29.10 (GND), U30.10 (GND)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
unnamed: D1.9 (K), R1.1
unnamed: D1.10 (K), R2.1
unnamed: D1.11 (K), R3.1
unnamed: D1.12 (K), R4.1
unnamed: D1.13 (K), R5.1
unnamed: D1.14 (K), R6.1
unnamed: D1.15 (K), R7.1
unnamed: D1.16 (K), R8.1
unnamed: D2.9 (K), R9.1
unnamed: D2.10 (K), R10.1
unnamed: D2.11 (K), R11.1
unnamed: D2.12 (K), R12.1
unnamed: D2.13 (K), R13.1
unnamed: D2.14 (K), R14.1
unnamed: D2.15 (K), R15.1
unnamed: D2.16 (K), R16.1
unnamed: D3.9 (K), R17.1
unnamed: D3.10 (K), R18.1
unnamed: D3.11 (K), R19.1
unnamed: D3.12 (K), R20.1
unnamed: D3.13 (K), R21.1
unnamed: D3.14 (K), R22.1
unnamed: D3.15 (K), R23.1
unnamed: D3.16 (K), R24.1
unnamed: D4.9 (K), R25.1
unnamed: D4.10 (K), R26.1
unnamed: D4.11 (K), R27.1
unnamed: D4.12 (K), R28.1
unnamed: D4.13 (K), R29.1
unnamed: D4.14 (K), R30.1
unnamed: D4.15 (K), R31.1
unnamed: D4.16 (K), R32.1
unnamed: D5.9 (K), R33.1
unnamed: D5.10 (K), R34.1
unnamed: D5.11 (K), R35.1
unnamed: D5.12 (K), R36.1
unnamed: D5.13 (K), R37.1
unnamed: D5.14 (K), R38.1
unnamed: D5.15 (K), R39.1
unnamed: D5.16 (K), R40.1
unnamed: D6.9 (K), R41.1
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
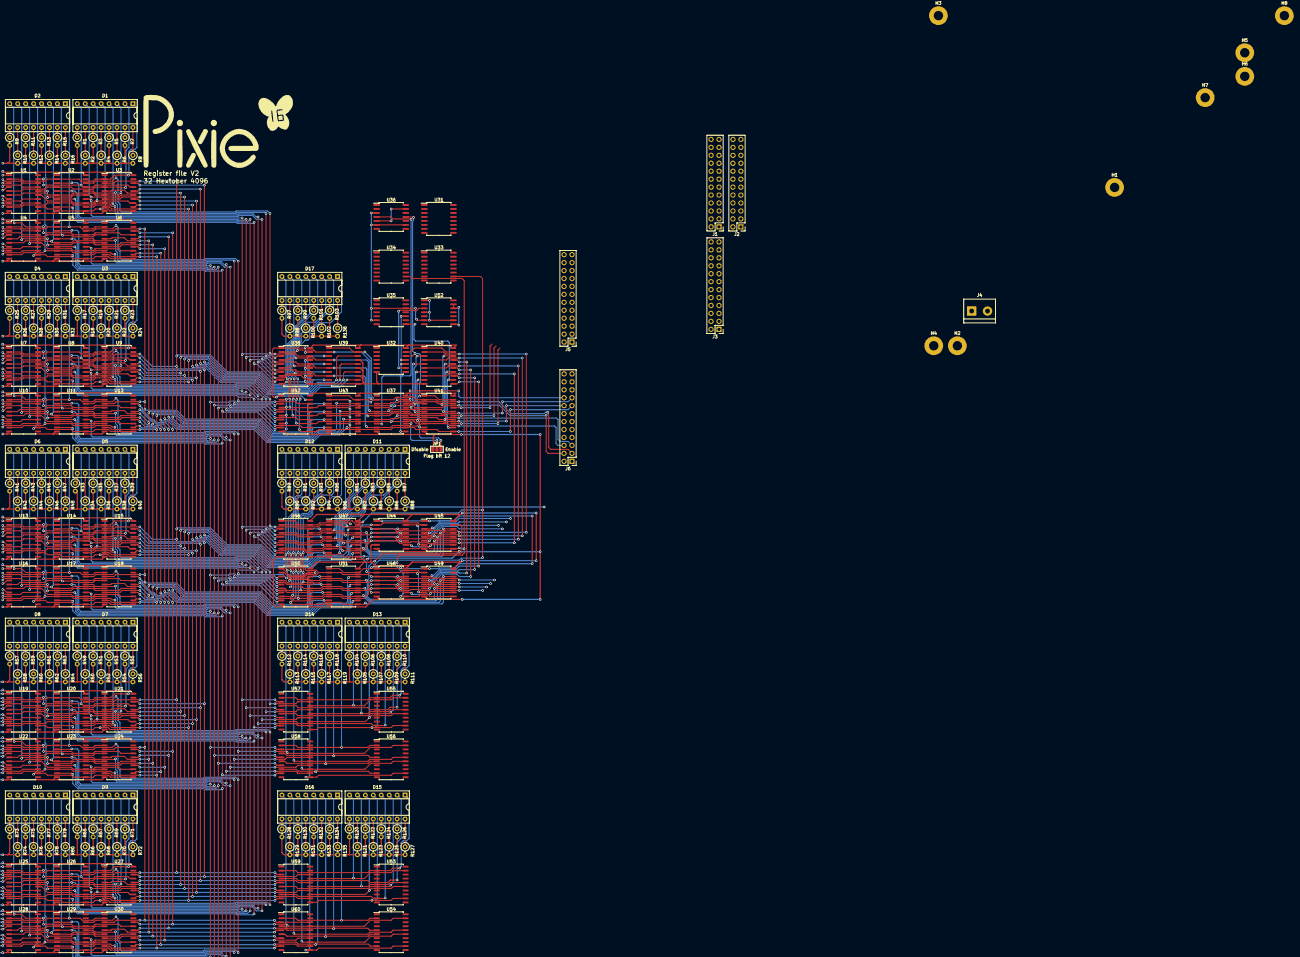
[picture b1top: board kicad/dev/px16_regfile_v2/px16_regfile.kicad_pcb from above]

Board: 2 copper layers, 228 parts (0 on the bottom side), 396 nets.
